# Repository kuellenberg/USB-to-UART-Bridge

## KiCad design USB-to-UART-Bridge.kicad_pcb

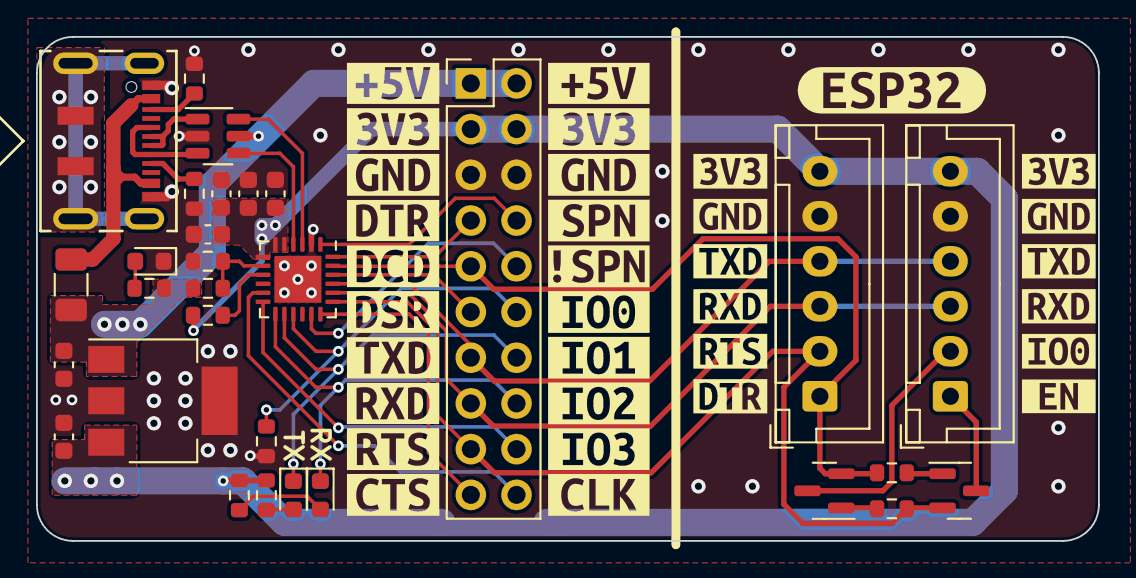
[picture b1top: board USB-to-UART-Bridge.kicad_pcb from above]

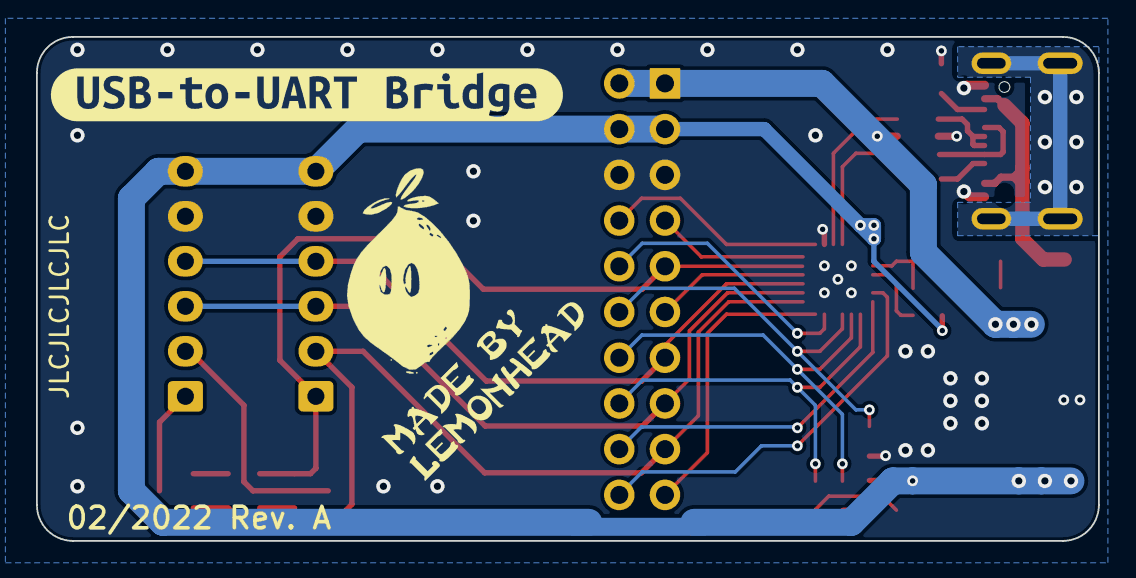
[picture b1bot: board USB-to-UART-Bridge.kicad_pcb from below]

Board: 2 copper layers, 59.0 x 28.0 mm, 65 parts (2 on the bottom side), 33 nets.

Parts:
C1, C3: 4.7uF; C_0603_1608Metric
C2, C4: 100nF; C_0603_1608Metric
C5, C6: 1uF; C_0603_1608Metric
D1, D2: LED_Red; LED_0603_1608Metric
D3: LED_Green; LED_0603_1608Metric
F1: Polyfuse, 0.5A; Fuse_1206_3216Metric
J1: USB_C_Receptacle_USB2.0; DX07S016JA3R1500
J2: Conn_02x10_Odd_Even; PinHeader_2x10_P2.54mm_Vertical
J3, J4: Conn_01x06; JST_XH_B6B-XH-A_1x06_P2.50mm_Vertical
Q1, Q2: BC848; SOT-23
R1, R2: 5.1k; R_0603_1608Metric
R3, R6, R8, R9: 1k; R_0603_1608Metric
R4: 22.1k; R_0603_1608Metric
R5: 47.5k; R_0603_1608Metric
R7: 10k (DNP); R_0603_1608Metric
R10, R11: 10k; R_0603_1608Metric
U1: USBLC6-2SC6; SOT-23-6
U2: CP2102N-Axx-xQFN24; QFN-24-1EP_4x4mm_P0.5mm_EP2.6x2.6mm
U3: MCP1703A-3302_SOT223; SOT-223-3_TabPin2
kibuzzard-61F83B56: G***; kibuzzard-61F83B56
kibuzzard-61FF9A0E: G***; kibuzzard-61FF9A0E
kibuzzard-61FF9A17: G***; kibuzzard-61FF9A17
kibuzzard-61FF9A21: G***; kibuzzard-61FF9A21
kibuzzard-61FF9A28: G***; kibuzzard-61FF9A28
kibuzzard-61FF9A38: G***; kibuzzard-61FF9A38
kibuzzard-61FF9B9B: G***; kibuzzard-61FF9B9B
kibuzzard-61FF9B79: G***; kibuzzard-61FF9B79
kibuzzard-61FF9B82: G***; kibuzzard-61FF9B82
kibuzzard-61FF9B89: G***; kibuzzard-61FF9B89
kibuzzard-61FF9B93: G***; kibuzzard-61FF9B93
kibuzzard-61FF9BA7: G***; kibuzzard-61FF9BA7
kibuzzard-61FF9BB1: G***; kibuzzard-61FF9BB1
kibuzzard-61FF9BB8: G***; kibuzzard-61FF9BB8
kibuzzard-61FF9BE1: G***; kibuzzard-61FF9BE1
kibuzzard-61FF9BED: G***; kibuzzard-61FF9BED
kibuzzard-61FF99E4: G***; kibuzzard-61FF99E4
kibuzzard-61FF99EF: G***; kibuzzard-61FF99EF
kibuzzard-61FF99FB: G***; kibuzzard-61FF99FB
kibuzzard-61FF9938: G***; kibuzzard-61FF9938
kibuzzard-61FF9957: G***; kibuzzard-61FF9957
kibuzzard-61FFA0CE, kibuzzard-61FFA0CE#2: G***; kibuzzard-61FFA0CE
kibuzzard-61FFA0DD, kibuzzard-61FFA0DD#2: G***; kibuzzard-61FFA0DD
kibuzzard-61FFA0EC, kibuzzard-61FFA0EC#2: G***; kibuzzard-61FFA0EC
kibuzzard-61FFA0F5, kibuzzard-61FFA0F5#2: G***; kibuzzard-61FFA0F5
kibuzzard-61FFA10B: G***; kibuzzard-61FFA10B
kibuzzard-61FFA13E: G***; kibuzzard-61FFA13E
kibuzzard-61FFA103: G***; kibuzzard-61FFA103
kibuzzard-61FFA126: G***; kibuzzard-61FFA126
kibuzzard-6204EF72: G***; kibuzzard-6204EF72
kibuzzard-6209BE0E: G***; kibuzzard-6209BE0E

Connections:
+3V3: C1.1, C2.1, C3.1, C4.1, C6.1, J2.3, J2.4, J3.6, J4.6, R6.1, R8.1, R9.1, U2.5 (VIO), U2.6 (VDD), U2.7 (VREGIN), U3.3 (VO)
/EN: J3.1, Q1.3 (C)
/GPIO2: J2.18, U2.12 (RS485/GPIO.2)
/GPIO3: J2.20, U2.11 (~WAKEUP/GPIO.3)
/IO0: J3.2, Q2.3 (C)
/RXD: J2.15, J3.3, J4.3, U2.20 (RXD)
/SUSPEND: J2.10, U2.17 (SUSPEND)
/TXD: J2.13, J3.4, J4.4, U2.21 (TXD)
/USB_CONN_DN: J1.A7 (D-), J1.B7 (D-), U1.3 (I/O2)
/USB_CONN_DP: J1.A6 (D+), J1.B6 (D+), U1.1 (I/O1)
/USB_DN: U1.4 (I/O2), U2.4 (D-)
/USB_DP: U1.6 (I/O1), U2.3 (D+)
/~CTS: J2.19, U2.18 (~CTS)
/~DCD: J2.7, U2.24 (~DCD)
/~DSR: J2.11, U2.22 (~DSR)
/~DTR: J2.9, J4.1, Q2.2 (E), R10.1, U2.23 (~DTR)
/~RI/CLK: J2.8, U2.1 (~RI/CLK)
/~RTS: J2.17, J4.2, Q1.2 (E), R11.1, U2.19 (~RTS)
/~RXT/GPIO1: D2.1 (K), J2.16, U2.13 (~RXT/GPIO.1)
/~SUSPEND: J2.12, R7.1, U2.15 (~SUSPEND)
/~TXT/GPIO0: D3.1 (K), J2.14, U2.14 (~TXT/GPIO.0)
GND: C1.2, C2.2, C3.2, C4.2, C5.2, C6.2, D1.1 (K), J1.A1 (GND), J1.A12 (GND), J2.5, J2.6, J3.5, J4.5, R1.1, R2.1, R5.2, R7.2, U1.2 (GND), U2.2 (GND), U2.25 (GND), U3.2 (GND)
unnamed: D1.2 (A), R3.2
unnamed: D2.2 (A), R8.2
unnamed: D3.2 (A), R9.2
unnamed: F1.1, J1.A4 (VBUS), J1.A9 (VBUS)
unnamed: J1.A5 (CC1), R1.2
unnamed: J1.B5 (CC2), R2.2
unnamed: Q1.1 (B), R10.2
unnamed: Q2.1 (B), R11.2
unnamed: R4.2, R5.1, U2.8 (VBUS)
unnamed: R6.2, U2.9 (~RST)
VBUS: C5.1, F1.2, J2.1, J2.2, R3.1, R4.1, U1.5 (VBUS), U3.1 (VI)

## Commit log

2022-08-24 Updated BOM
